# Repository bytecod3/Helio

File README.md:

# Dual-Axis Solar Tracking
Optimize absortion of sun's energy by use of light intensity measurements whose different values make a solar panel to rotate towards the direction of the sun.
The data from the solar tracker is sent to a through an ESP2266 module to the owner for them to know when the batterries being charged are full.

### Working
The circuit uses two LDRs as inputs to ATMEGA328P. The arduino compares the voltages and tilts the servo motor connected to one of the pins to the side that is receiving more sunlight. The program ensures that the solar panel is always oriented 90 degress towards the sun for optimum photovoltaic generation ef energy.

# Schematic

### PCB Layout

### PCB Top View

### PCB Side View

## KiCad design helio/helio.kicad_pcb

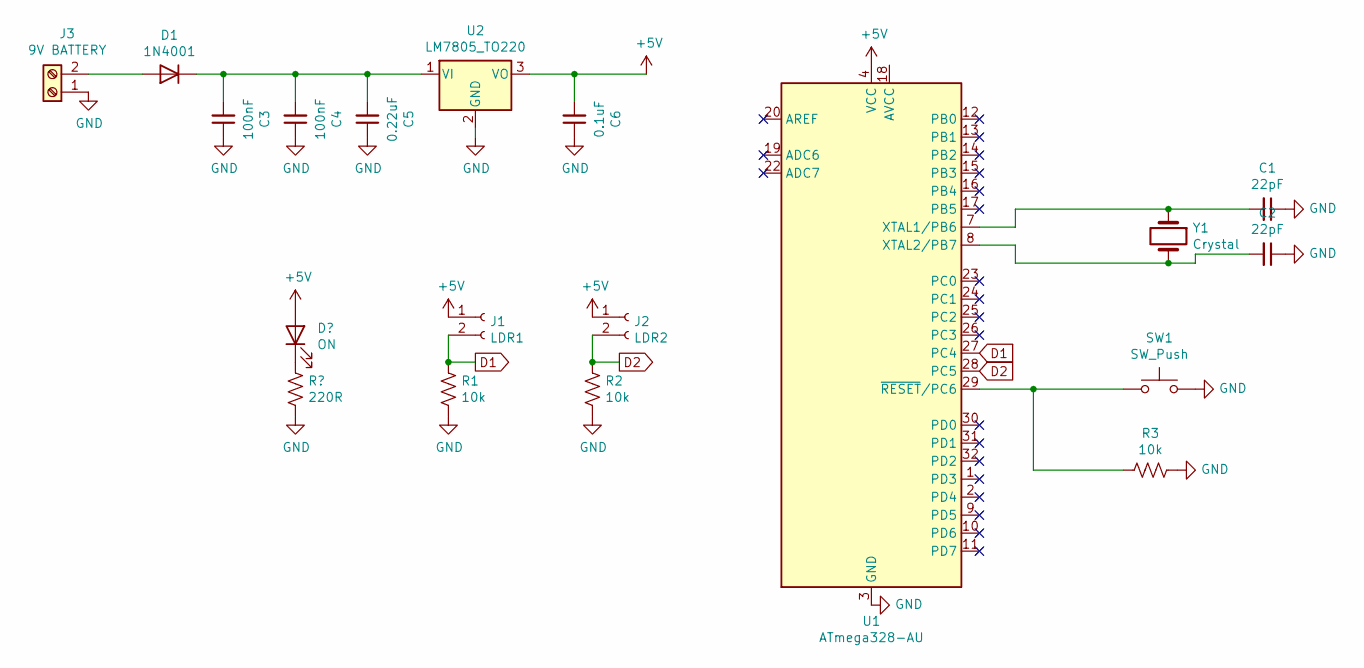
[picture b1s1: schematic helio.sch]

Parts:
C1, C2: 22pF; C_0603_1608Metric
C3, C4: 100nF; C_0603_1608Metric
C5: 0.22uF; C_0603_1608Metric
C6: 0.1uF; C_0603_1608Metric
D1: 1N4001; D_DO-41_SOD81_P10.16mm_Horizontal
J1: LDR1; JST_EH_B2B-EH-A_1x02_P2.50mm_Vertical
J2: LDR2; JST_EH_B2B-EH-A_1x02_P2.50mm_Vertical
J3: 9V BATTERY; JST_EH_B2B-EH-A_1x02_P2.50mm_Vertical
R1, R2, R3: 10k; R_0603_1608Metric
SW1: SW_Push; SW_SPST_TL3342
U1: ATmega328-AU; TQFP-32_7x7mm_P0.8mm
U2: LM7805_TO220; TO-220-3_Vertical
Y1: Crystal; Crystal_SMD_HC49-SD_HandSoldering

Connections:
+5V: C6.2, J1.1, J2.1, U1.4 (VCC), U1.6 (VCC), U2.3 (VO); also elsewhere on the board
D1: J1.2, R1.2, U1.27 (PC4)
D2: J2.2, R2.1, U1.28 (PC5)
GND: C1.1, C2.1, C3.1, C4.1, C5.1, C6.1, J3.1, R1.1, R2.2, R3.1, SW1.2, U1.3 (GND), U1.5 (GND), U1.21 (GND), U2.2 (GND); also elsewhere on the board
unnamed: C1.2, U1.7 (XTAL1/PB6), Y1.1
unnamed: C2.2, U1.8 (XTAL2/PB7), Y1.2
unnamed: C3.2, C4.2, C5.2, D1.1 (K), U2.1 (VI)
unnamed: D1.2 (A), J3.2
unnamed: R3.2, SW1.1, U1.29 (~RESET~/PC6)

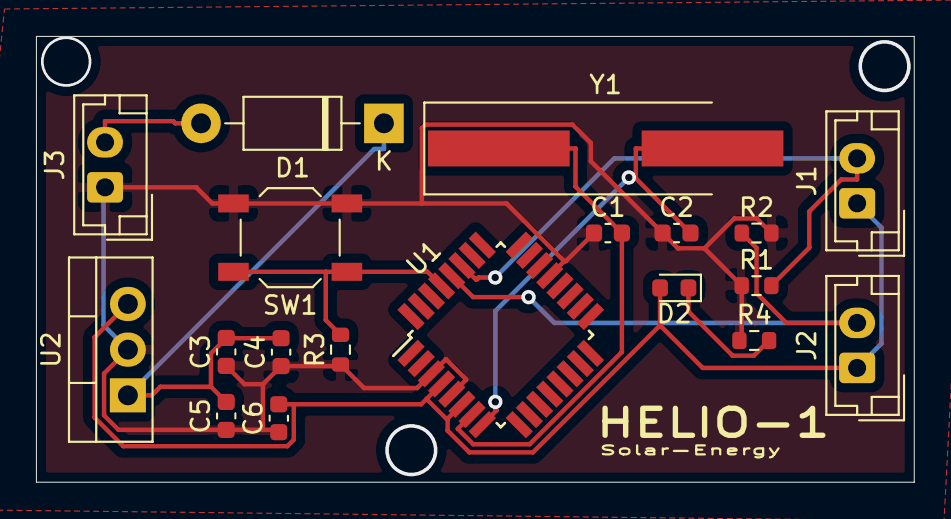
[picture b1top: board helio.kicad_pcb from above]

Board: 2 copper layers, 48.8 x 24.8 mm, 19 parts (0 on the bottom side), 10 nets.

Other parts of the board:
D2: ON; LED_0603_1608Metric
R4: 220R; R_0603_1608Metric

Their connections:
+5V: D2.2; also elsewhere on the board
GND: R4.1; also elsewhere on the board
unnamed: D2.1, R4.2

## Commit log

2020-02-21 Create servo_control.ino
    Arduino code to control panel rotation with servo
2020-02-21 Create server.ino
    esp module code
2020-02-21 Servo control using python
2020-02-21 code to send data over network test run one
2020-02-24 included function to measure battery voltage
    To measure battery voltage more than 5V on analog pin
2021-03-01 added schematics
2021-05-07 Added real time LDR value graphing with matplotlib
2021-05-07 Added graph
2021-10-20 redesigned schematic and PCB
